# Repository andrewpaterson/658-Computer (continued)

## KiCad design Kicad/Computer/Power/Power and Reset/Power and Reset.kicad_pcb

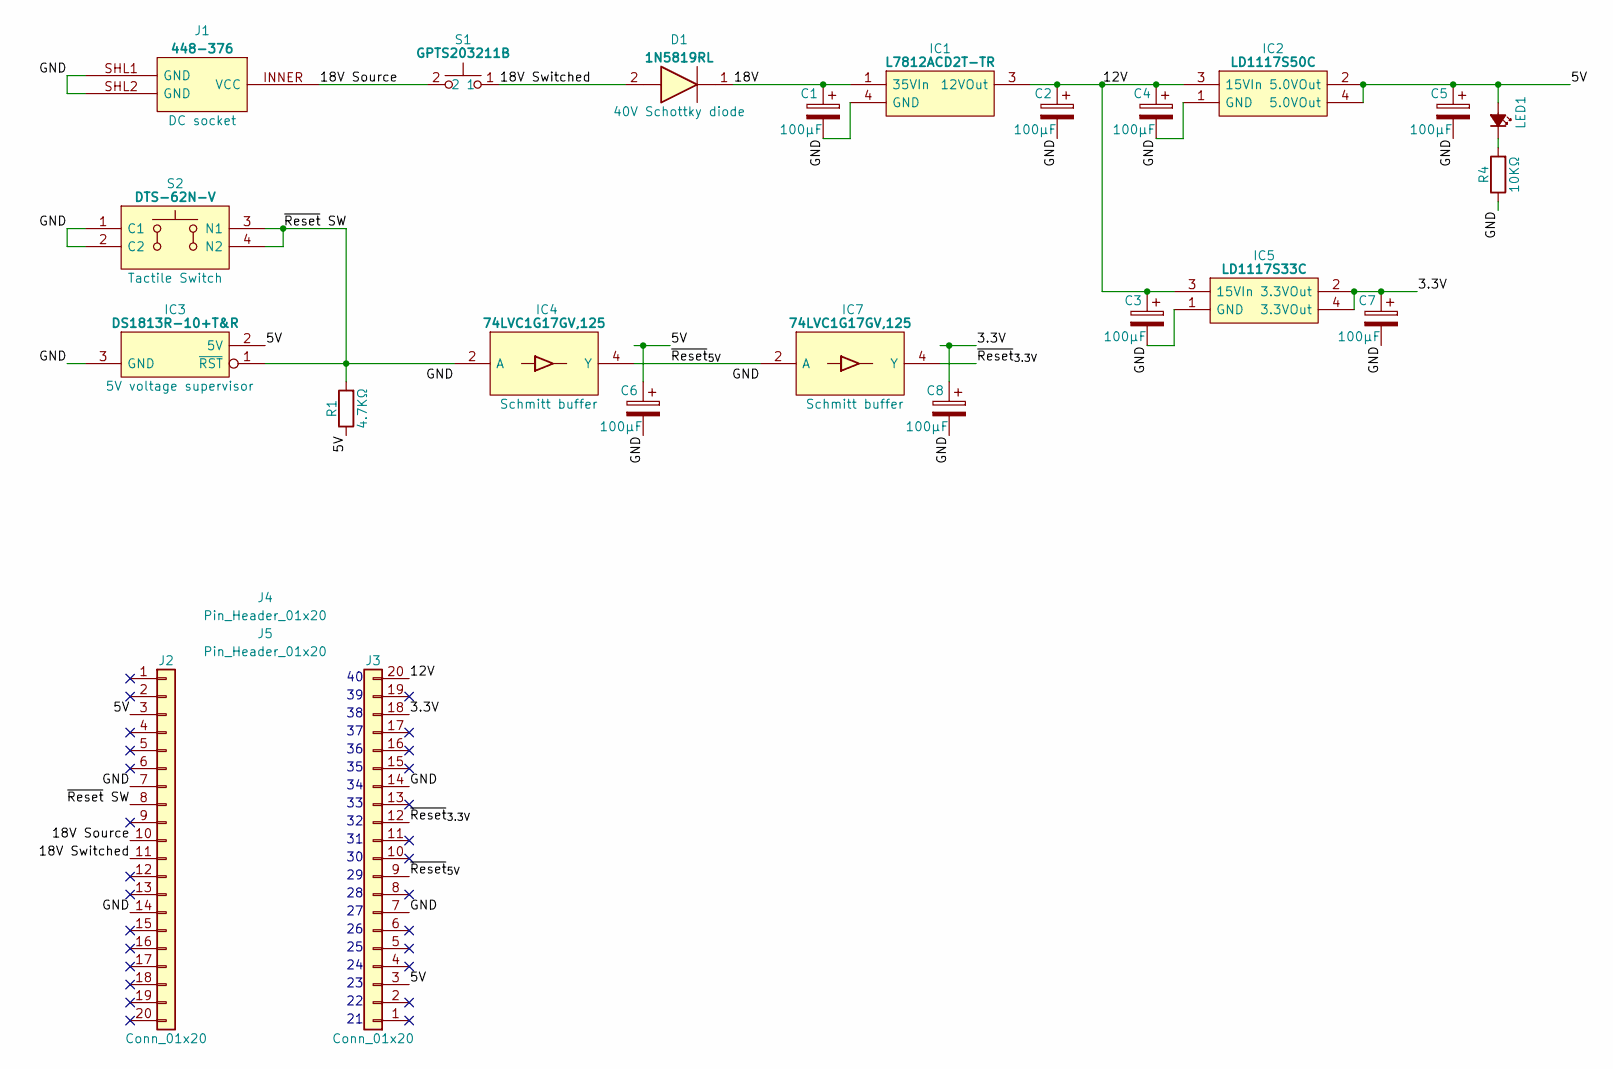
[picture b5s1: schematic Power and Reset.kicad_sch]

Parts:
C1, C2, C3, C4, C5, C6, C7, C8: 100μF; CP_Radial_D6.3mm_P2.50mm
D1: 1N5819RL; DIOAD1414W86L464D238; Manufacturer_Part_Number 1N5819RL; Mouser Part Number 511-1N5819-TR
IC1: L7812ACD2T-TR; TO254P1542X460-3N; Manufacturer_Part_Number L7812ACD2T-TR
IC2: LD1117S50C; LD1117S33C; Manufacturer_Part_Number LD1117S50C
IC3: DS1813R-10+T&R; SOT95P237X112-3N; Mouser Part Number 700-DS1813R-10T&R
IC4, IC7: 74LVC1G17GV,125; SOT95P275X110-5N; Manufacturer_Part_Number 74LVC1G17GV,125
IC5: LD1117S33C; Manufacturer_Part_Number LD1117S33C
J1: 448-376; 448376; Manufacturer_Part_Number 448-376
J2, J3: Conn_01x20; SIP_20_Pins
J4, J5: Pin_Header_01x20; PinHeader_1x20_P2.54mm_Vertical
LED1: LED_Small_Filled; LED_D5.0mm
R1: 4.7KΩ; R_Axial_DIN0204_L3.6mm_D1.6mm_P5.08mm_Horizontal
R4: 10KΩ; R_Axial_DIN0204_L3.6mm_D1.6mm_P5.08mm_Horizontal
S1: GPTS203211B; Manufacturer_Part_Number GPTS203211B; Mouser Part Number 629-GPTS203211B
S2: DTS-62N-V; DTS62NV; Manufacturer_Part_Number DTS-62N-V; Mouser Part Number 113-DTS-62N-V

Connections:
/3.3V: C7.1, C8.1, IC5.2 (3.3VOut), IC5.4 (3.3VOut), IC7.5 (3V), J3.18
/5V: C5.1, C6.1, IC2.2 (5.0VOut), IC2.4 (5.0VOut), IC3.2 (5V), IC4.5 (3V), J2.3, J3.3, LED1.2 (A), R1.1
/12V: C2.1, C3.1, C4.1, IC1.3 (12VOut), IC2.3 (15VIn), IC5.3 (15VIn), J3.20
/18V: C1.1, D1.1, IC1.1 (35VIn)
/18V Source: J1.INNER (VCC), J2.10, S1.2
/18V Switched: D1.2, J2.11, S1.1
/GND: C1.2, C2.2, C3.2, C4.2, C5.2, C6.2, C7.2, C8.2, IC1.4 (GND), IC2.1 (GND), IC3.3 (GND), IC4.3 (GND), IC5.1 (GND), IC7.3 (GND), J1.SHL1 (GND), J1.SHL2 (GND), J2.7, J2.14, J3.7, J3.14, R4.1, S2.1 (C1), S2.2 (C2)
/~Reset SW: IC3.1 (~RST), IC4.2 (A), J2.8, R1.2, S2.3 (N1), S2.4 (N2)
/~Reset_{3.3V}: IC7.4 (Y), J3.12
/~Reset_{5V}: IC4.4 (Y), IC7.2 (A), J3.9
unnamed: LED1.1 (K), R4.2

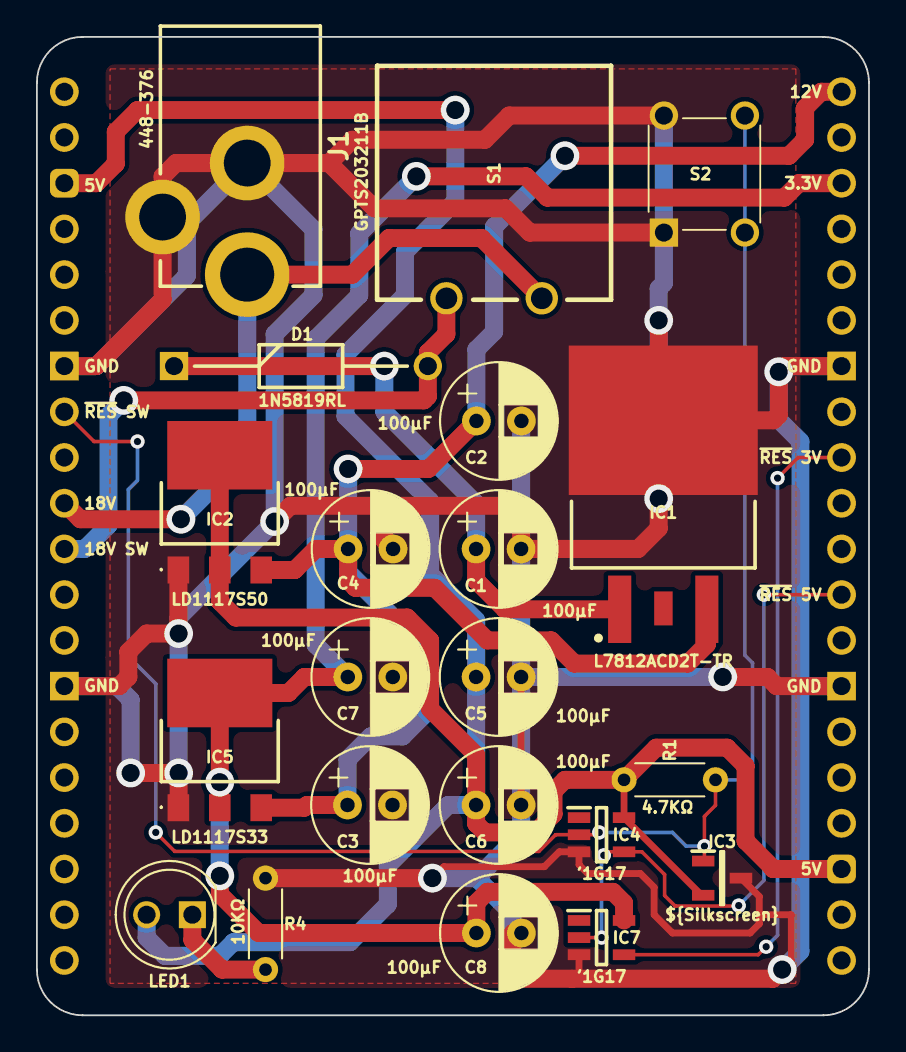
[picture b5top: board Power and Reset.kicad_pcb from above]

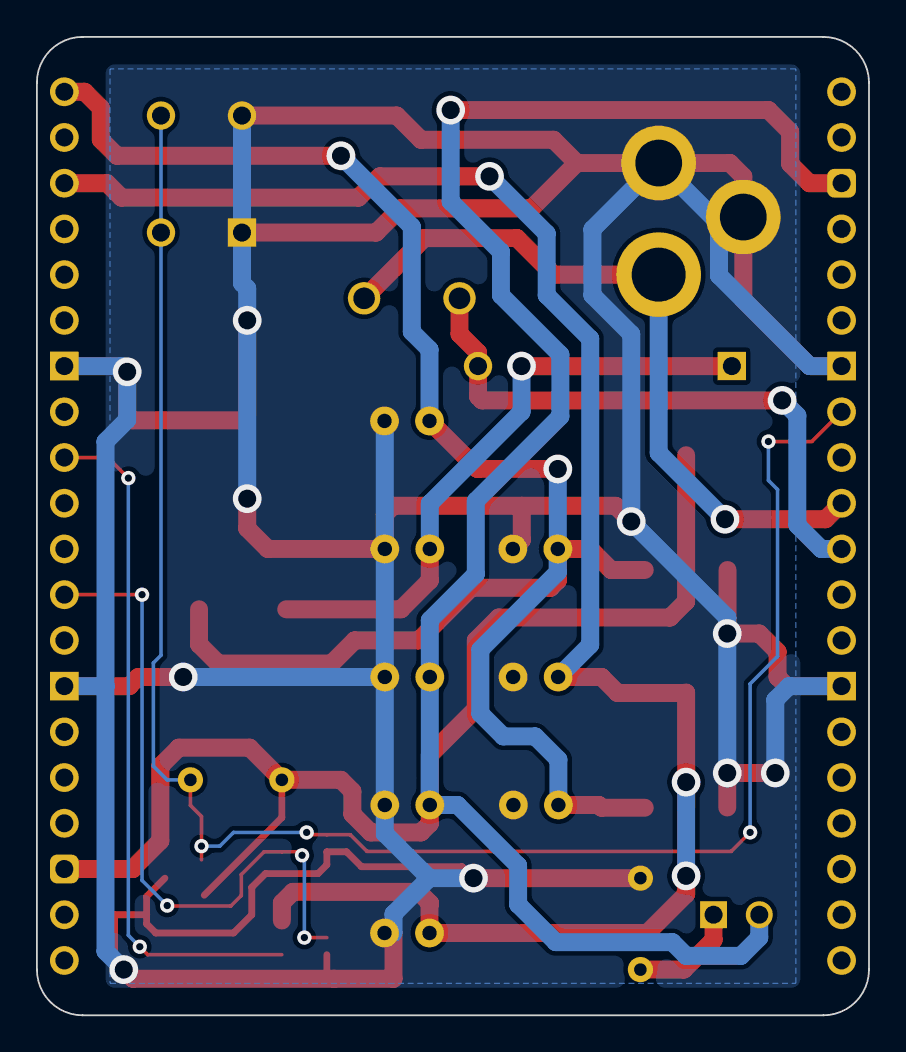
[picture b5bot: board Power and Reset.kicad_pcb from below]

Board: 2 copper layers, 46.2 x 54.4 mm, 25 parts (2 on the bottom side), 11 nets.

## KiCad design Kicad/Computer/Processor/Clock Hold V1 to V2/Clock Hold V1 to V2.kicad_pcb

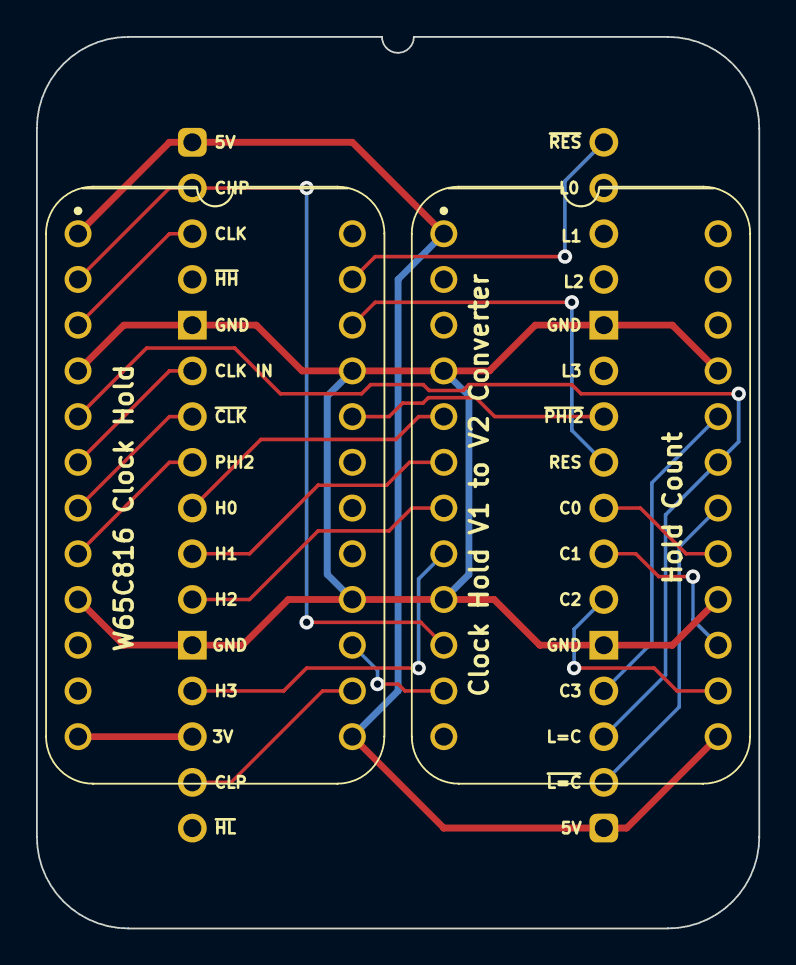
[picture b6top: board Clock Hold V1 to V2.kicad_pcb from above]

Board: 2 copper layers, 40.1 x 49.5 mm, 3 parts (0 on the bottom side), 23 nets.

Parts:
B22: W65C816 Clock Hold; HCP65_W65C816_Clock_Hold
B23: Hold Count; HCP65_Hold_Count
J1: Board 2x16 W22.86mm; DIP-32_Board_W22.86mm_Nak

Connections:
3.3V: B22.12 (~Hold_Low), J1.14
5V: B22.1 (5V), B22.13 (5V), B23.1 (5V), B23.13 (5V), J1.1, J1.17
/~CHP: B22.15 (~CLK_High_Pulse), B23.11 (~CLK_High_Pulse)
C0: B23.17 (Count0), J1.24
C1: B23.15 (Count1), J1.23
C2: B23.14 (Count2), J1.22
C3: B23.20 (Count3), J1.20
CHP: B22.2 (CLK_High_Pulse), B23.10 (CLK_High_Pulse), J1.2
CLK: B22.3 (CLK), J1.3
CLK IN: B22.6 (CLK_IN), J1.6
CLP: B22.14 (CLK_Low_Pulse), J1.15
GND: B22.4 (GND), B22.9 (GND), B22.16 (GND), B22.21 (GND), B23.4 (GND), B23.9 (GND), B23.16 (GND), B23.21 (GND), J1.5, J1.12, J1.21, J1.28
H0: B23.5 (Hold0), J1.9
H1: B23.6 (Hold1), J1.10
H2: B23.7 (Hold2), J1.11
H3: B23.8 (Hold3), J1.13
L=C: B22.5 (~Hold_High), B23.19 (L=C), J1.19
PHI2: B22.8 (PHI2), J1.8
Reset: B22.22 (Reset), J1.25
~CLK: B22.7 (~CLK), J1.7
~L=C: B23.18 (~L=C), J1.18
~PHI2: B22.20 (~PHI2), J1.26
~Reset: B22.23 (~Reset), J1.32

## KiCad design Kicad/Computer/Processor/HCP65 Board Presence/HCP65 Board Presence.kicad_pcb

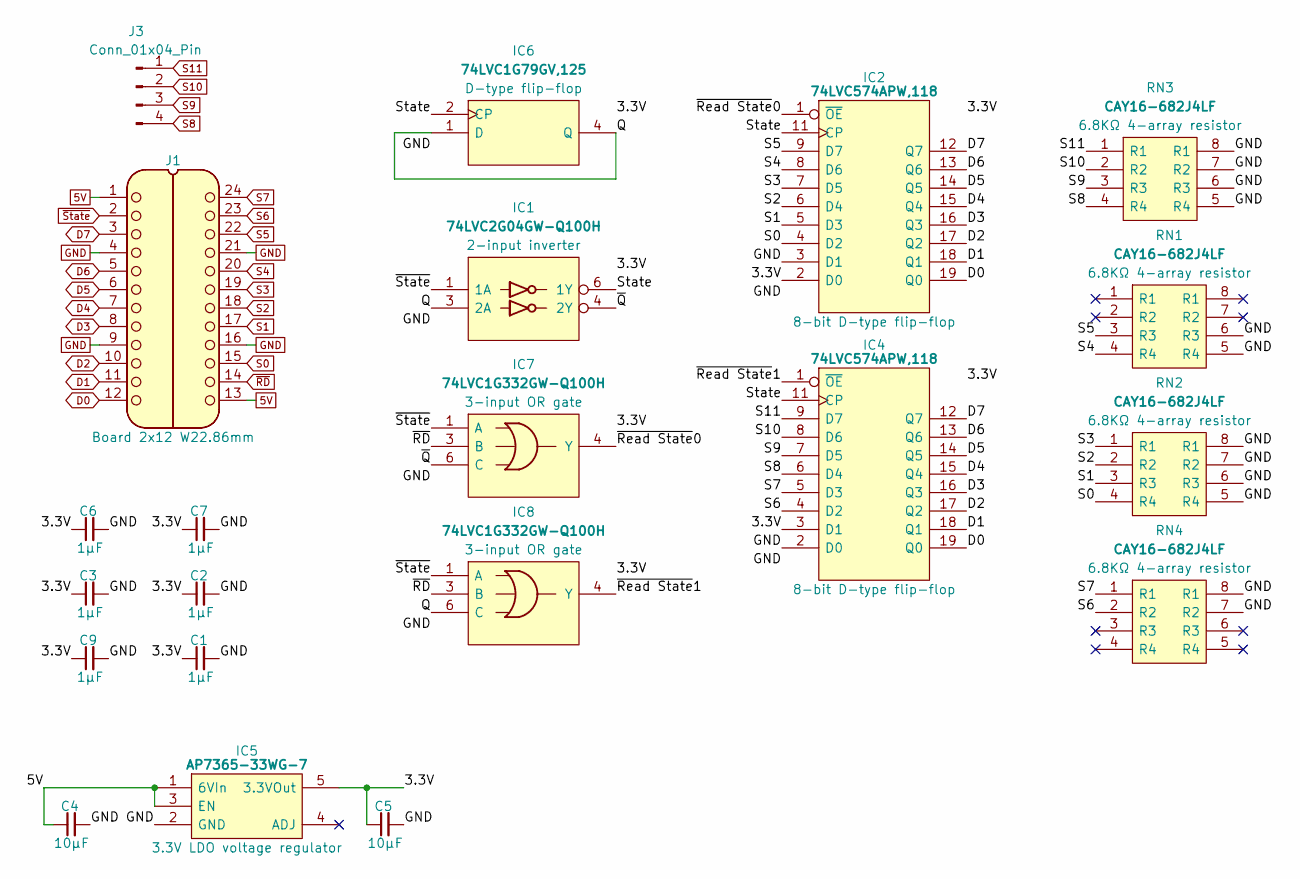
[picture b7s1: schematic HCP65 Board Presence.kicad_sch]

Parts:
C1, C2, C3, C6, C7, C9: 1μF; C_0805
C4, C5: 10µF; C_0805
IC1: 74LVC2G04GW-Q100H; SOP65P210X110-6N; Manufacturer_Part_Number 74LVC2G04GW-Q100H; Mouser Part Number 771-74LVC2G04GWQ100H
IC2, IC4: 74LVC574APW,118; SOP65P640X110-20N; Mouser Part Number 771-74LVC574APW-T
IC5: AP7365-33WG-7; SOT95P285X130-5N; Manufacturer_Part_Number AP7365-33WG-7; Mouser Part Number 621-AP7365-33WG-7
IC6: 74LVC1G79GV,125; SOT95P275X110-5N; Mouser Part Number 771-LVC1G79GV125
IC7, IC8: 74LVC1G332GW-Q100H; SOP65P210X110-6N; Mouser Part Number 771-74LVC1G332GWQ100
J1: Board 2x12 W22.86mm; DIP-24_Board_W22.86mm
J3: Conn_01x04_Pin; PinHeader_1x04_P2.54mm_Vertical
RN1, RN2, RN3, RN4: CAY16-682J4LF; CAY16-J4

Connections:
5V: C4.1, IC5.1 (6VIn), IC5.3 (EN), J1.1, J1.13
/3.3V: C1.1, C2.1, C3.1, C5.1, C6.1, C7.1, C9.1, IC1.5 (3V), IC2.2 (D0), IC2.20 (3V), IC4.3 (D1), IC4.20 (3V), IC5.5 (3.3VOut), IC6.5 (3V), IC7.5 (3V), IC8.5 (3V)
/Q: IC1.3 (2A), IC6.1 (D), IC6.4 (Q), IC8.6 (C)
/State: IC1.6 (1Y), IC2.11 (CP), IC4.11 (CP), IC6.2 (CP)
/~Q: IC1.4 (2Y), IC7.6 (C)
/~Read State0: IC2.1 (~OE), IC7.4 (Y)
/~Read State1: IC4.1 (~OE), IC8.4 (Y)
D0: IC2.19 (Q0), IC4.19 (Q0), J1.12
D1: IC2.18 (Q1), IC4.18 (Q1), J1.11
D2: IC2.17 (Q2), IC4.17 (Q2), J1.10
D3: IC2.16 (Q3), IC4.16 (Q3), J1.8
D4: IC2.15 (Q4), IC4.15 (Q4), J1.7
D5: IC2.14 (Q5), IC4.14 (Q5), J1.6
D6: IC2.13 (Q6), IC4.13 (Q6), J1.5
D7: IC2.12 (Q7), IC4.12 (Q7), J1.3
GND: C1.2, C2.2, C3.2, C4.2, C5.2, C6.2, C7.2, C9.2, IC1.2 (GND), IC2.3 (D1), IC2.10 (GND), IC4.2 (D0), IC4.10 (GND), IC5.2 (GND), IC6.3 (GND), IC7.2 (GND), IC8.2 (GND), J1.4, J1.9, J1.16, J1.21, RN1.5 (R4), RN1.6 (R3), RN2.5 (R4), RN2.6 (R3), RN2.7 (R2), RN2.8 (R1), RN3.5 (R4), RN3.6 (R3), RN3.7 (R2), RN3.8 (R1), RN4.7 (R2), RN4.8 (R1)
S0: IC2.4 (D2), J1.15, RN2.4 (R4)
S1: IC2.5 (D3), J1.17, RN2.3 (R3)
S2: IC2.6 (D4), J1.18, RN2.2 (R2)
S3: IC2.7 (D5), J1.19, RN2.1 (R1)
S4: IC2.8 (D6), J1.20, RN1.4 (R4)
S5: IC2.9 (D7), J1.22, RN1.3 (R3)
S6: IC4.4 (D2), J1.23, RN4.2 (R2)
S7: IC4.5 (D3), J1.24, RN4.1 (R1)
S8: IC4.6 (D4), J3.4, RN3.4 (R4)
S9: IC4.7 (D5), J3.3, RN3.3 (R3)
S10: IC4.8 (D6), J3.2, RN3.2 (R2)
S11: IC4.9 (D7), J3.1, RN3.1 (R1)
~RD: IC7.3 (B), IC8.3 (B), J1.14
~State: IC1.1 (1A), IC7.1 (A), IC8.1 (A), J1.2

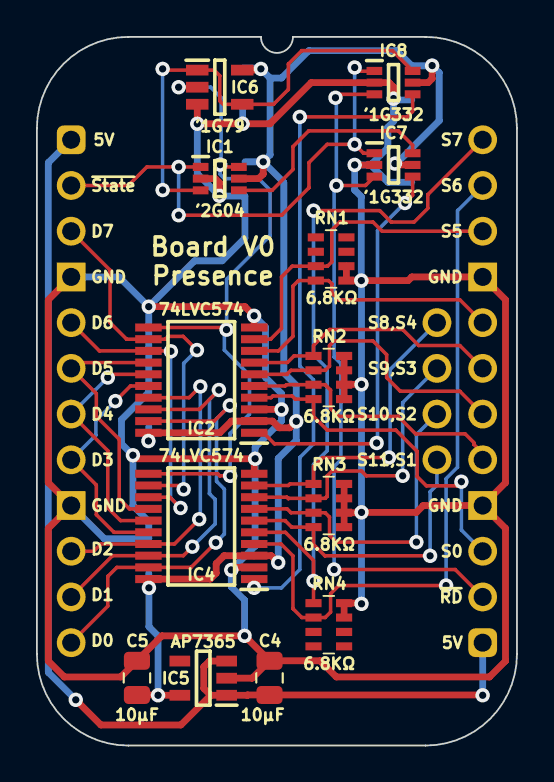
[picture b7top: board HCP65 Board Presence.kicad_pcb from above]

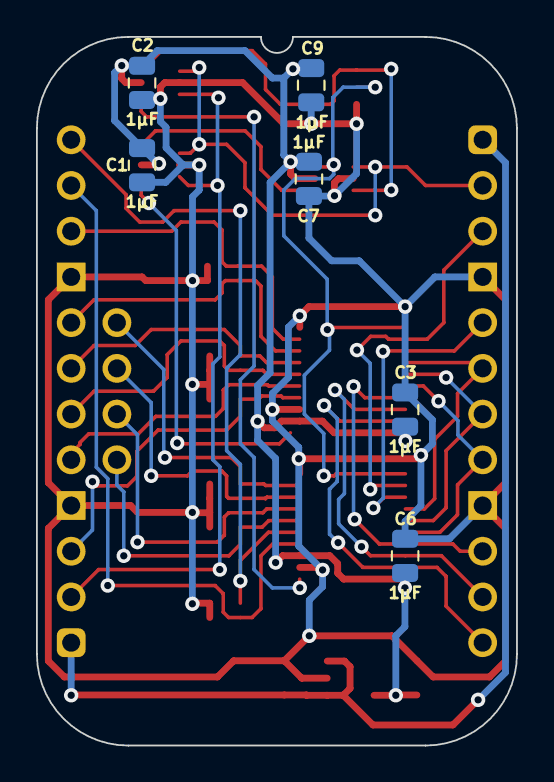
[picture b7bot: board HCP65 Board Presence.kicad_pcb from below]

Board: 2 copper layers, 26.7 x 39.4 mm, 21 parts (7 on the bottom side), 30 nets.
